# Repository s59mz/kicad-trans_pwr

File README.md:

# kicad-trans_pwr
Simple Power Supply made by main transformer and voltage dubler.
It generates +12V, -12V and +5V voltages with linear voltage generators.

Schematic:
[kicad-trans_pwr.pdf](kicad-trans_pwr.pdf)

BOM:
[kicad-trans_pwr.csv](kicad-trans_pwr.csv)

Gerbers:
[gerbers.zip](https://github.com/s59mz/kicad-trans_pwr/raw/main/gerbers.zip)

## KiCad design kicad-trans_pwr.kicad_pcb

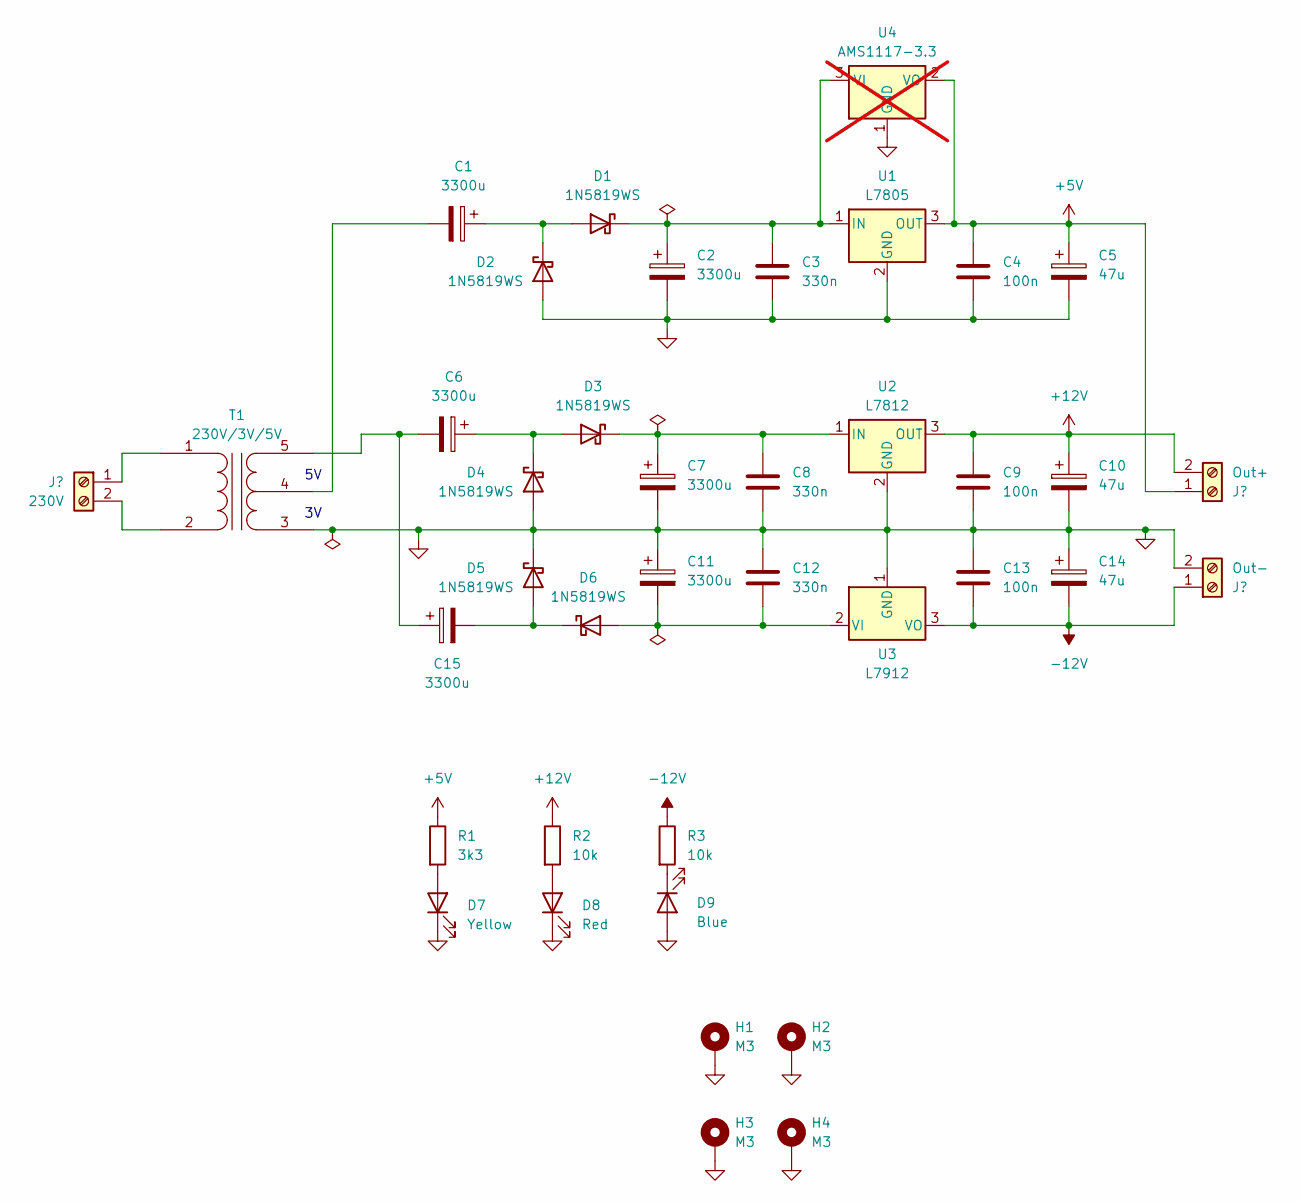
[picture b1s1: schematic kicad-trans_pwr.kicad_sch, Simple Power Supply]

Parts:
C1, C2, C6, C7, C11, C15: 3300u; CP_Radial_D16.0mm_P7.50mm
C3, C8, C12: 330n; C_Disc_D5.0mm_W2.5mm_P5.00mm
C4, C9, C13: 100n; C_Disc_D5.0mm_W2.5mm_P5.00mm
C5, C10, C14: 47u; CP_Radial_D5.0mm_P2.50mm
D1, D2, D3, D4, D5, D6: 1N5819WS; D_SOD-123
D7: Yellow; LED_0603_1608Metric_Pad1.05x0.95mm_HandSolder
D8: Red; LED_0603_1608Metric_Pad1.05x0.95mm_HandSolder
D9: Blue; LED_0603_1608Metric_Pad1.05x0.95mm_HandSolder
H1, H2, H3, H4: M3; MountingHole_3.2mm_M3_Pad
J1: 230V; TerminalBlock_bornier-2_P5.08mm
J2: Out+; TerminalBlock_bornier-2_P5.08mm
J3: Out-; TerminalBlock_bornier-2_P5.08mm
R1: 3k3; R_0603_1608Metric_Pad0.98x0.95mm_HandSolder
R2, R3: 10k; R_0603_1608Metric_Pad0.98x0.95mm_HandSolder
T1: 230V/3V/5V; Transformer_43x43
U1: L7805; TO-220-3_Horizontal_TabGND
U2: L7812; TO-220-3_Horizontal_TabGND
U3: L7912; TO-220-3_Horizontal_TabDown
U4: AMS1117-3.3; SOT-223-3_TabPin2; not fitted

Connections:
+5V: C4.1, C5.1, J2.1, R1.1, U1.3 (OUT), U4.2 (VO)
+12V: C9.1, C10.1, J2.2, R2.1, U2.3 (OUT)
-12V: C13.2, C14.2, J3.1, R3.1, U3.3 (VO)
GND: C2.2, C3.2, C4.2, C5.2, C7.2, C8.2, C9.2, C10.2, C11.1, C12.1, C13.1, C14.1, D2.2 (A), D4.2 (A), D5.1 (K), D7.1 (K), D8.1 (K), D9.2 (A), H1.1, H2.1, H3.1, H4.1, J3.2, T1.3 (SA), U1.2 (GND), U2.2 (GND), U3.1 (GND), U4.1 (GND)
unnamed: C1.1, D1.2 (A), D2.1 (K)
unnamed: C2.1, C3.1, D1.1 (K), U1.1 (IN), U4.3 (VI)
unnamed: C6.1, D3.2 (A), D4.1 (K)
unnamed: C7.1, C8.1, D3.1 (K), U2.1 (IN)
unnamed: C15.2, D5.2 (A), D6.1 (K)
unnamed: C11.2, C12.2, D6.2 (A), U3.2 (VI)
unnamed: D7.2 (A), R1.2
unnamed: D8.2 (A), R2.2
unnamed: D9.1 (K), R3.2
unnamed: J1.1, T1.1 (AA)
unnamed: J1.2, T1.2 (AB)
unnamed: C6.2, C15.1, T1.5 (SB)
unnamed: C1.2, T1.4 (SC)

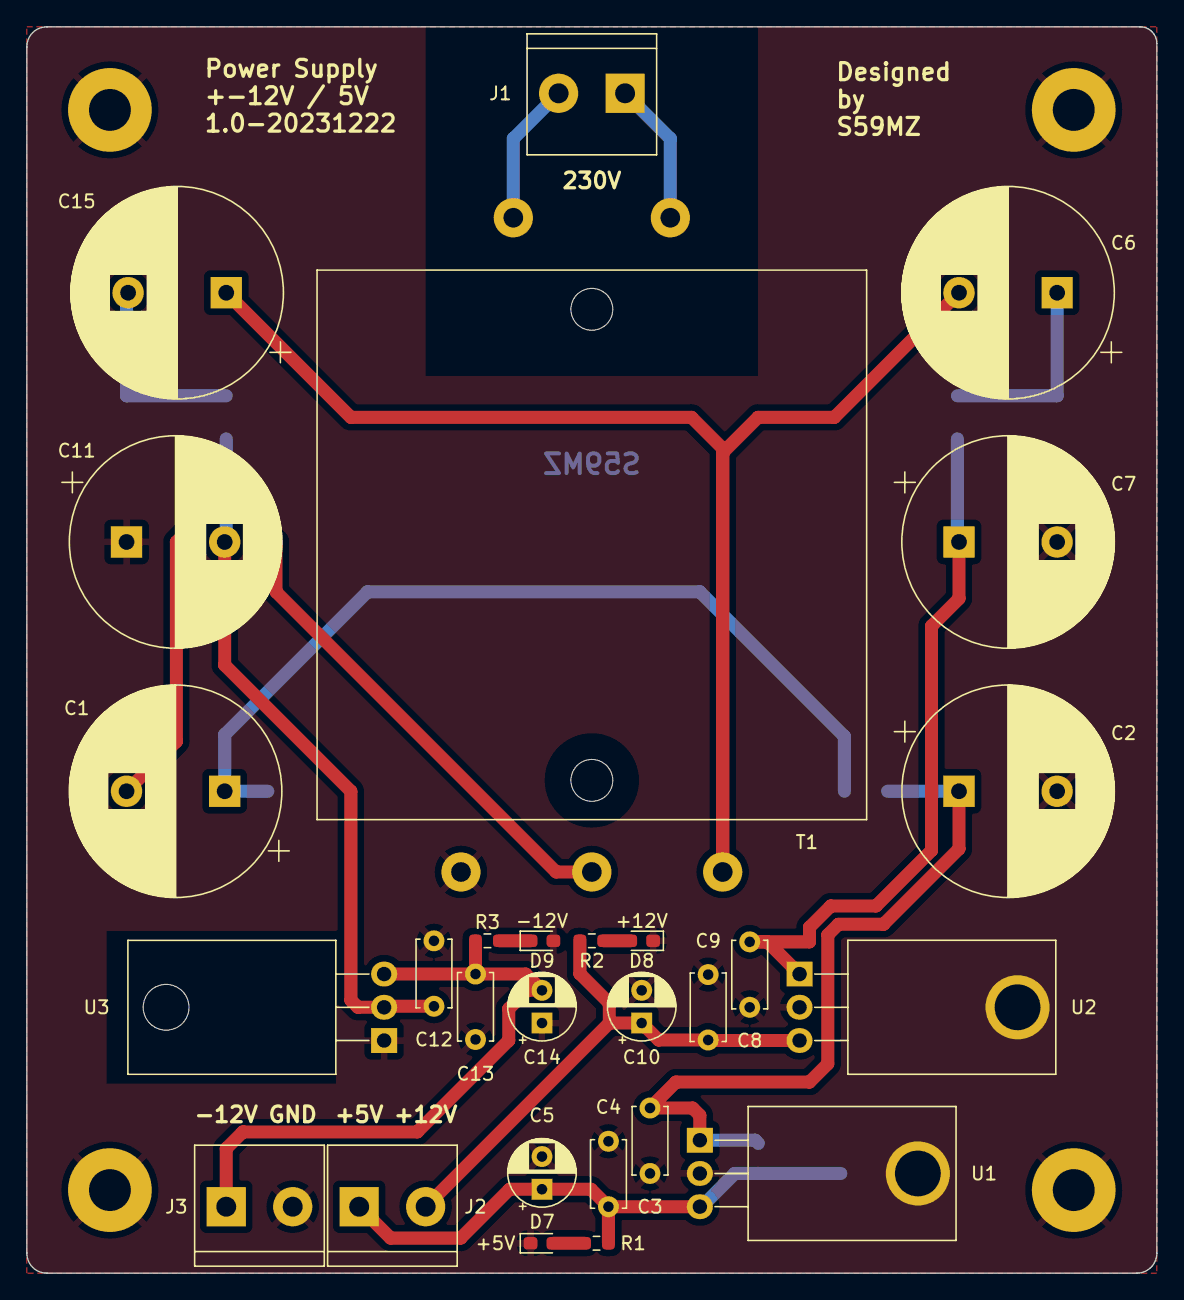
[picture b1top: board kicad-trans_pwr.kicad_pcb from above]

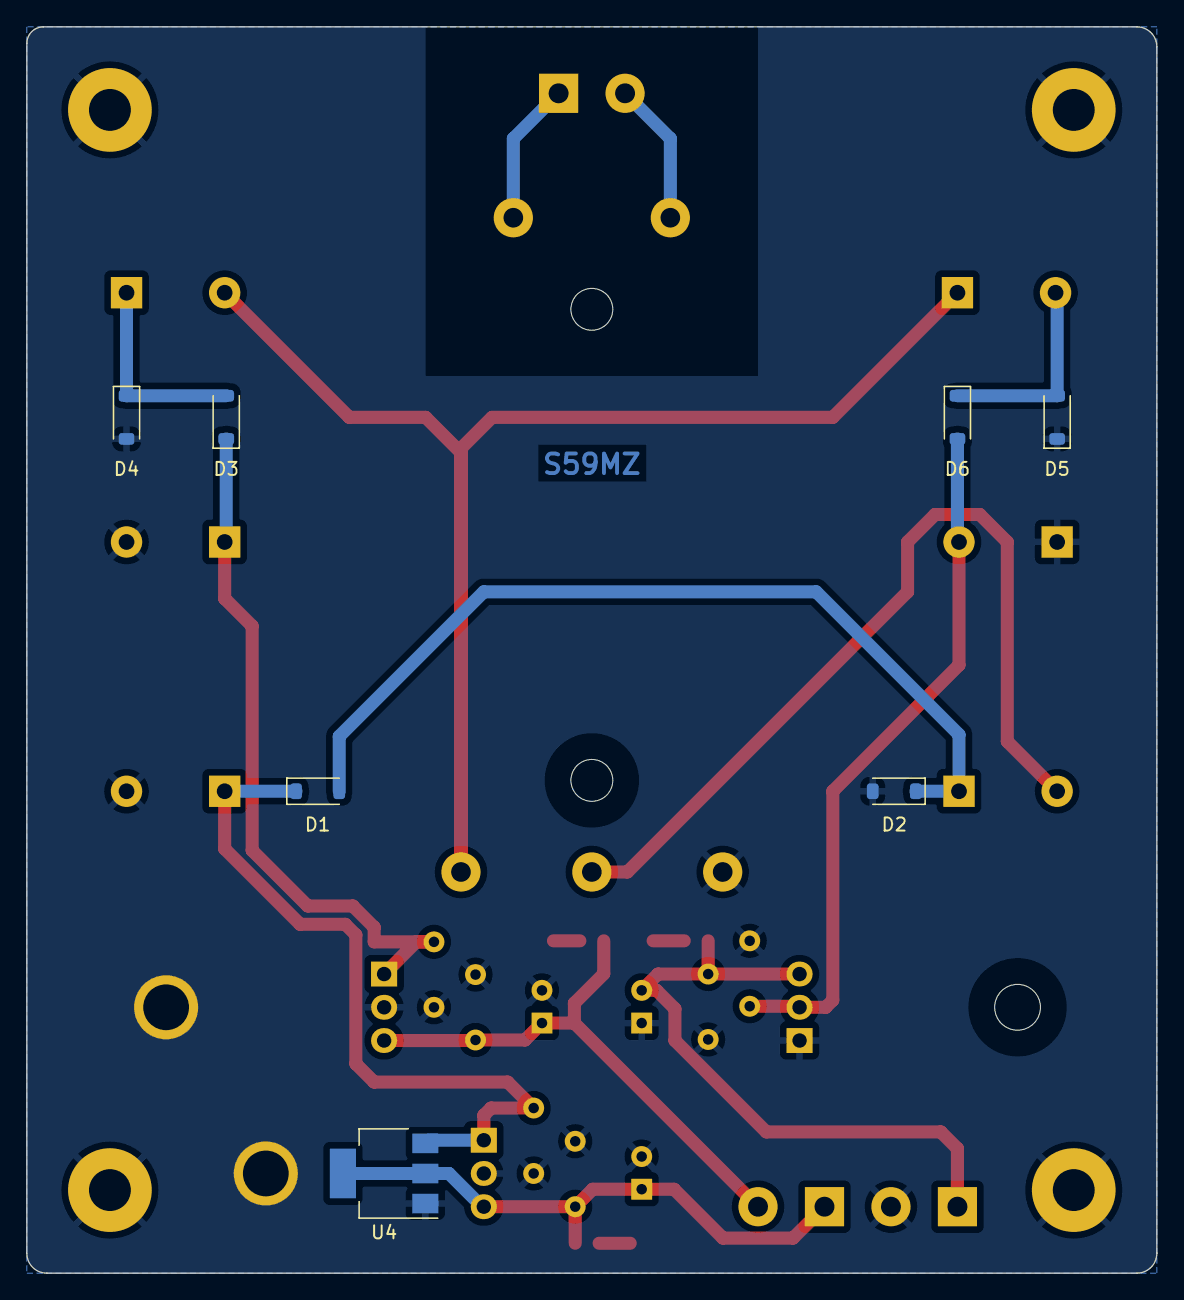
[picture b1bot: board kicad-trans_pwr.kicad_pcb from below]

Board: 2 copper layers, 86.4 x 95.2 mm, 39 parts (7 on the bottom side), 17 nets.
